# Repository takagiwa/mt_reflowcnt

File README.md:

# mt_reflowcnt

Reflow Toaster Controller clone

Original is here: https://www.switch-science.com/products/1690

You can use their software: https://github.com/SWITCHSCIENCE/Dual_SSR_Solder_Toaster_Controller_Platform/

You need Arduino Uno or compatible board. 5V I/O needed.

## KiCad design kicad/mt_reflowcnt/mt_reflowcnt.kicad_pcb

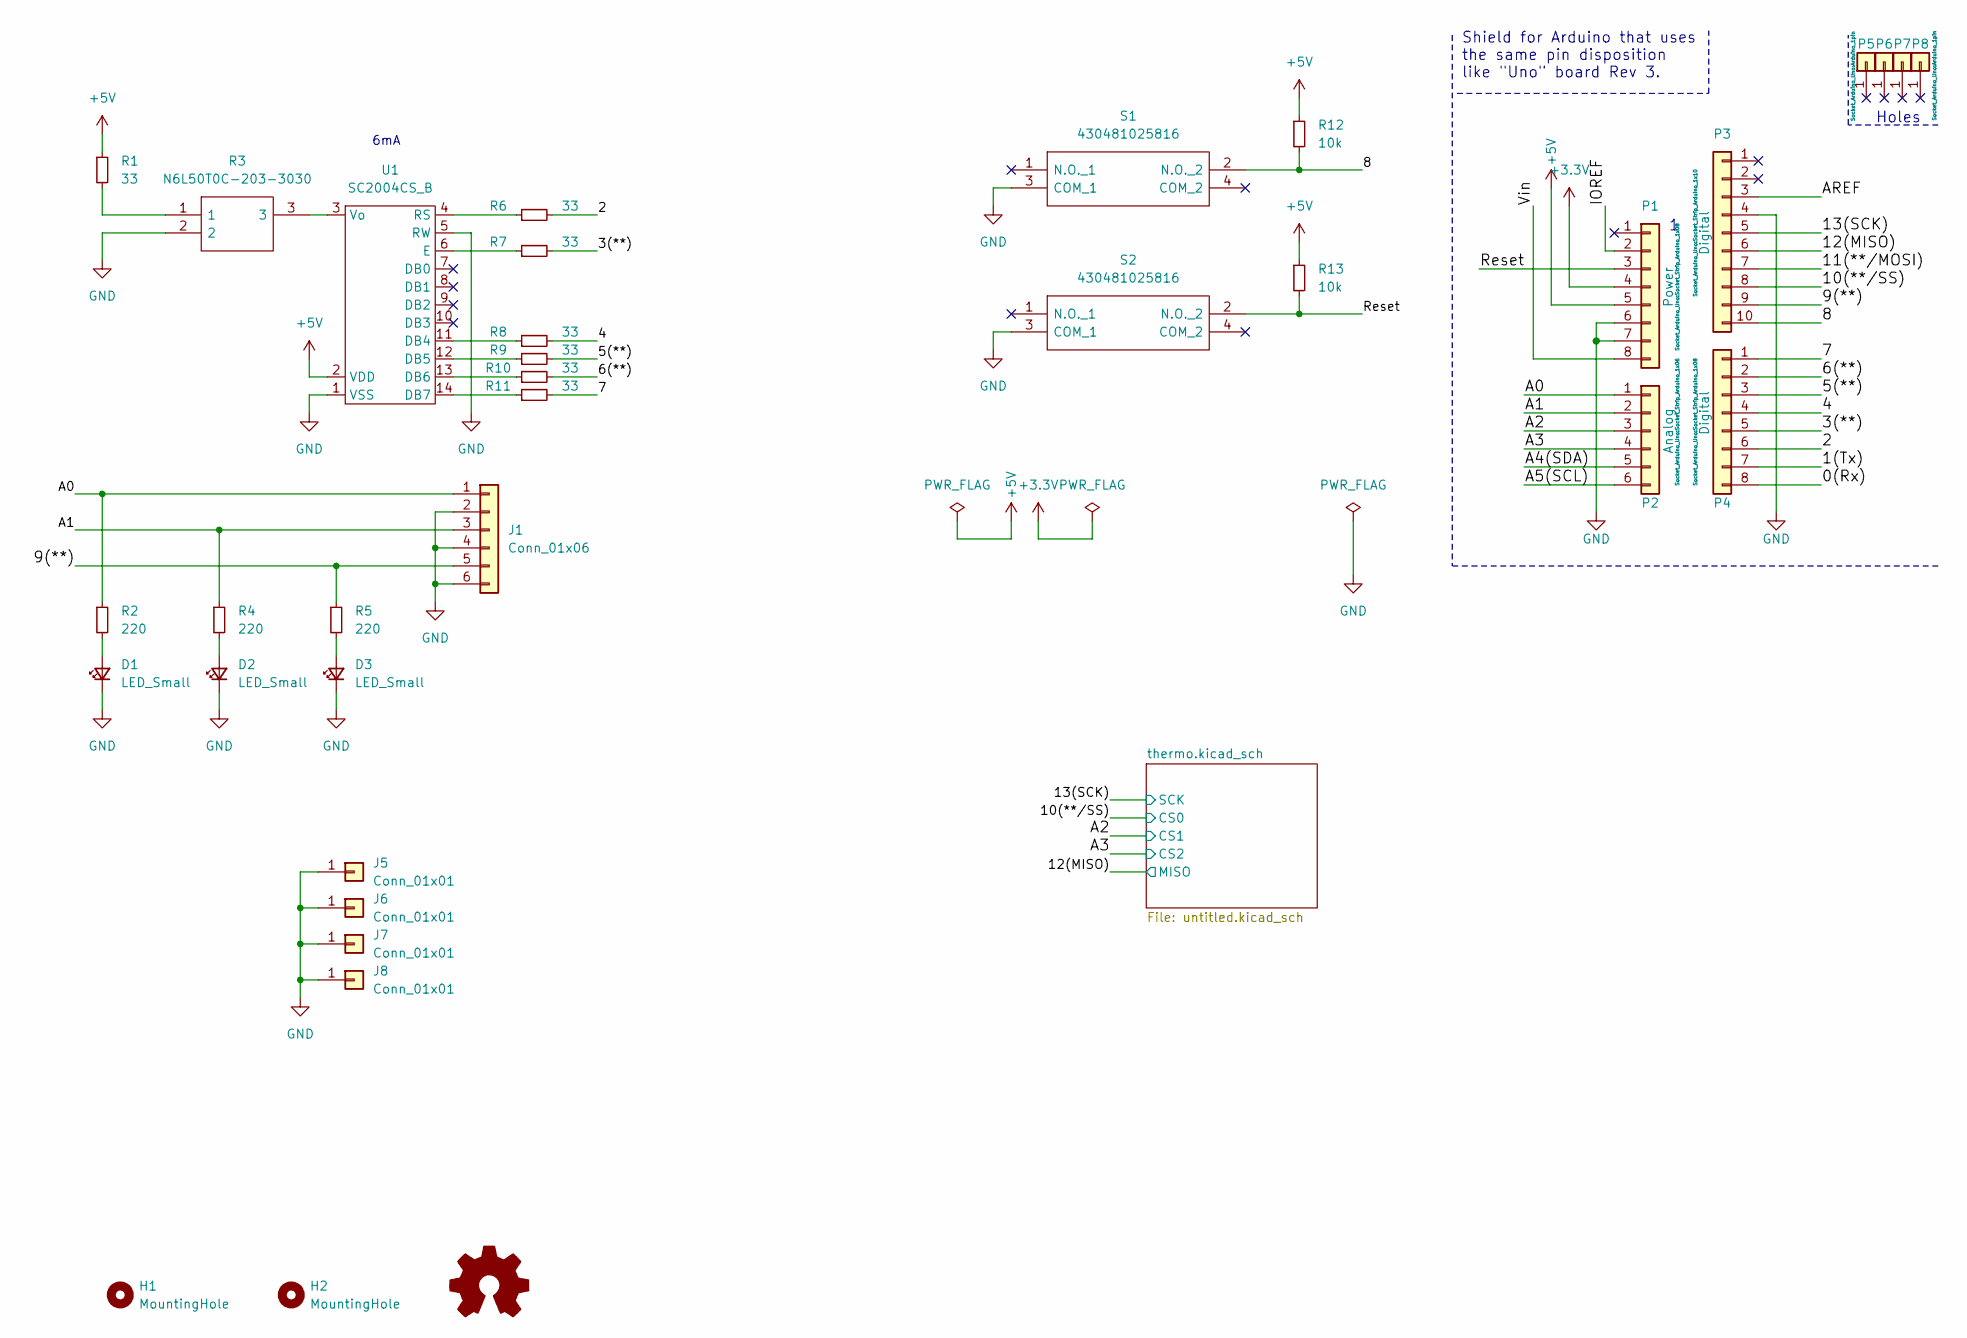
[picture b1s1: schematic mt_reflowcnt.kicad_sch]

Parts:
D1, D2, D3: LED_Small; LED_0805_2012Metric_Pad1.15x1.40mm_HandSolder
H1, H2: MountingHole; MountingHole_3.2mm_M3
J1: Conn_01x06; PinHeader_1x06_P2.54mm_Vertical
J5, J6, J7, J8: Conn_01x01; PinSocket_1x01_P2.54mm_Vertical
P1: Power; Socket_Strip_Arduino_1x08
P2: Analog; Socket_Strip_Arduino_1x06
P3: Digital; Socket_Strip_Arduino_1x10
P4: Digital; Socket_Strip_Arduino_1x08
P5, P6, P7, P8: CONN_01X01; Arduino_1pin
R1, R6, R7, R8, R9, R10, R11: 33; R_0805_2012Metric_Pad1.20x1.40mm_HandSolder
R2, R4, R5: 220; R_0805_2012Metric_Pad1.20x1.40mm_HandSolder
R3: N6L50T0C-203-3030; N6L50T0C2033030; Mouser Part Number 531-N6L50T0C2033030
R12, R13: 10k; R_0805_2012Metric_Pad1.20x1.40mm_HandSolder
S1, S2: 430481025816; Mouser Part Number 710-430481025816
U1: SC2004CS_B

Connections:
+3.3V: P1.4; also elsewhere on the board
+5V: P1.5, R1.1, R12.1, R13.1, U1.2 (VDD); also elsewhere on the board
/0(Rx): P4.8
/1(Tx): P4.7
/2: P4.6, R6.2
/3(**): P4.5, R7.2
/4: P4.4, R8.2
/5(**): P4.3, R9.2
/6(**): P4.2, R10.2
/7: P4.1, R11.2
/8: P3.10, R12.2, S1.2 (N.O._2)
/9(**): J1.5, P3.9, R5.1
/10(**/SS): P3.8; also elsewhere on the board
/11(**/MOSI): P3.7
/12(MISO): P3.6; also elsewhere on the board
/13(SCK): P3.5; also elsewhere on the board
/A0: J1.1, P2.1, R2.1
/A1: J1.3, P2.2, R4.1
/A2: P2.3; also elsewhere on the board
/A3: P2.4; also elsewhere on the board
/A4(SDA): P2.5
/A5(SCL): P2.6
/AREF: P3.3
/IOREF: P1.2
/Reset: P1.3, R13.2, S2.2 (N.O._2)
/Vin: P1.8
GND: D1.1 (K), D2.1 (K), D3.1 (K), J1.2, J1.4, J1.6, J5.1, J6.1, J7.1, J8.1, P1.6, P1.7, P3.4, R3.2, S1.3 (COM_1), S2.3 (COM_1), U1.1 (VSS), U1.5 (RW); also elsewhere on the board
unnamed: D1.2 (A), R2.2
unnamed: D2.2 (A), R4.2
unnamed: D3.2 (A), R5.2
unnamed: R1.2, R3.1
unnamed: R3.3, U1.3 (Vo)
unnamed: R6.1, U1.4 (RS)
unnamed: R7.1, U1.6 (E)
unnamed: R8.1, U1.11 (DB4)
unnamed: R9.1, U1.12 (DB5)
unnamed: R10.1, U1.13 (DB6)
unnamed: R11.1, U1.14 (DB7)

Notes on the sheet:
Holes
Shield for Arduino that uses the same pin disposition like "Uno" board Rev 3.
6mA

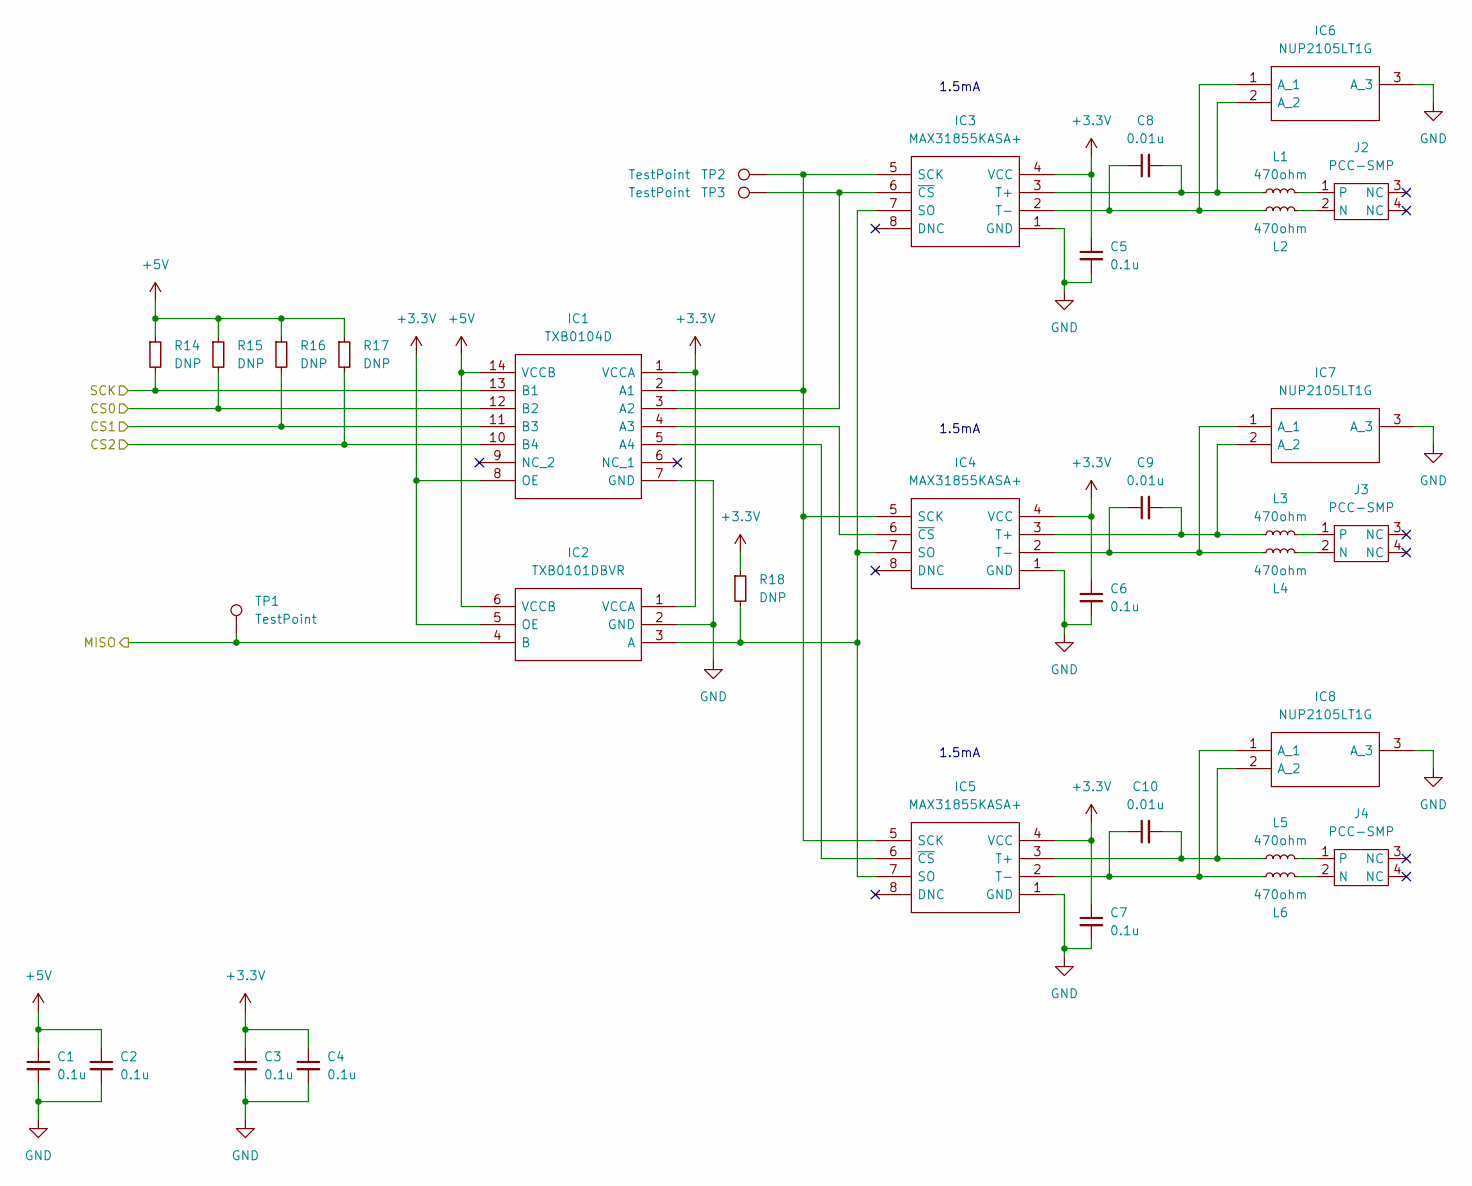
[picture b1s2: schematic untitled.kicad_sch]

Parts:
C1, C2, C3, C4, C5, C6, C7: 0.1u; C_0805_2012Metric_Pad1.18x1.45mm_HandSolder
C8, C9, C10: 0.01u; C_0805_2012Metric_Pad1.18x1.45mm_HandSolder
IC1: TXB0104D; SOIC127P600X175-14N; Mouser Part Number 595-TXB0104D
IC2: TXB0101DBVR; SOT95P280X145-6N; Mouser Part Number 595-TXB0101DBVR
IC3, IC4, IC5: MAX31855KASA+; SOIC127P600X175-8N; Mouser Part Number 700-MAX31855KASA+
IC6, IC7, IC8: NUP2105LT1G; SOT96P237X111-3N; Mouser Part Number 863-NUP2105LT1G
J2, J3, J4: PCC-SMP
L1, L2, L3, L4, L5, L6: 470ohm; L_0603_1608Metric_Pad1.05x0.95mm_HandSolder
R14, R15, R16, R17, R18: DNP; R_0805_2012Metric_Pad1.20x1.40mm_HandSolder
TP1, TP2, TP3: TestPoint; TestPoint_Pad_D2.0mm

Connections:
+3.3V: C3.1, C4.1, C5.1, C6.1, C7.1, IC1.1 (VCCA), IC1.8 (OE), IC2.1 (VCCA), IC2.5 (OE), IC3.4 (VCC), IC4.4 (VCC), IC5.4 (VCC), R18.1; also elsewhere on the board
+5V: C1.1, C2.1, IC1.14 (VCCB), IC2.6 (VCCB), R14.1, R15.1, R16.1, R17.1; also elsewhere on the board
/10(**/SS): IC1.12 (B2), R15.2; also elsewhere on the board
/12(MISO): IC2.4 (B), TP1.1; also elsewhere on the board
/13(SCK): IC1.13 (B1), R14.2; also elsewhere on the board
/A2: IC1.11 (B3), R16.2; also elsewhere on the board
/A3: IC1.10 (B4), R17.2; also elsewhere on the board
GND: C1.2, C2.2, C3.2, C4.2, C5.2, C6.2, C7.2, IC1.7 (GND), IC2.2 (GND), IC3.1 (GND), IC4.1 (GND), IC5.1 (GND), IC6.3 (A), IC7.3 (A), IC8.3 (A); also elsewhere on the board
unnamed: C8.1, IC3.2 (T-), IC6.1 (A), L2.1
unnamed: C8.2, IC3.3 (T+), IC6.2 (A), L1.1
unnamed: C9.1, IC4.2 (T-), IC7.1 (A), L4.1
unnamed: C9.2, IC4.3 (T+), IC7.2 (A), L3.1
unnamed: C10.1, IC5.2 (T-), IC8.1 (A), L6.1
unnamed: C10.2, IC5.3 (T+), IC8.2 (A), L5.1
unnamed: IC1.2 (A1), IC3.5 (SCK), IC4.5 (SCK), IC5.5 (SCK), TP2.1
unnamed: IC1.3 (A2), IC3.6 (~CS), TP3.1
unnamed: IC1.4 (A3), IC4.6 (~CS)
unnamed: IC1.5 (A4), IC5.6 (~CS)
unnamed: IC2.3 (A), IC3.7 (SO), IC4.7 (SO), IC5.7 (SO), R18.2
unnamed: J2.1, L1.2
unnamed: J2.2 (N), L2.2
unnamed: J3.1, L3.2
unnamed: J3.2 (N), L4.2
unnamed: J4.1, L5.2
unnamed: J4.2 (N), L6.2

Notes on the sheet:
1.5mA

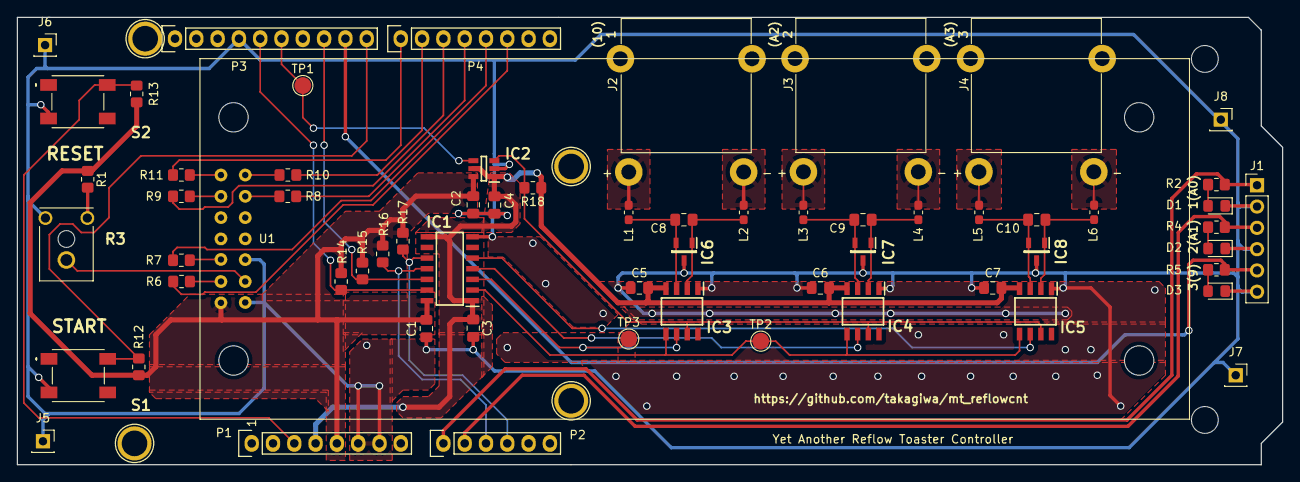
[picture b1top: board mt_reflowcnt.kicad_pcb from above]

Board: 2 copper layers, 150.9 x 53.3 mm, 69 parts (0 on the bottom side), 47 nets.

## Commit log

2022-07-18 initial version
2022-11-03 first refined version. add more thermocouple and add one more relay control.
2022-11-03 unwanted file
2022-11-03 add link
2023-01-30 レベルシフタの方向を修正
